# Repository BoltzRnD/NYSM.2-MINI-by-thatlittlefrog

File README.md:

# NYSM.2-MINI

NYSM.2 compatible full featured TMC2209 stepper driver with a smaller footprint than standard NYSM.2

It's around half the size of the original NYSM.2 driver, occupying a "2215" footprint rather than 2230, the smallest size seen on commercial M.2 drives.

### Future versions: 
* Cleaner routing
* Better thermals
* Custom low profile heatsink
* Onboard setting jumpers for microstepping

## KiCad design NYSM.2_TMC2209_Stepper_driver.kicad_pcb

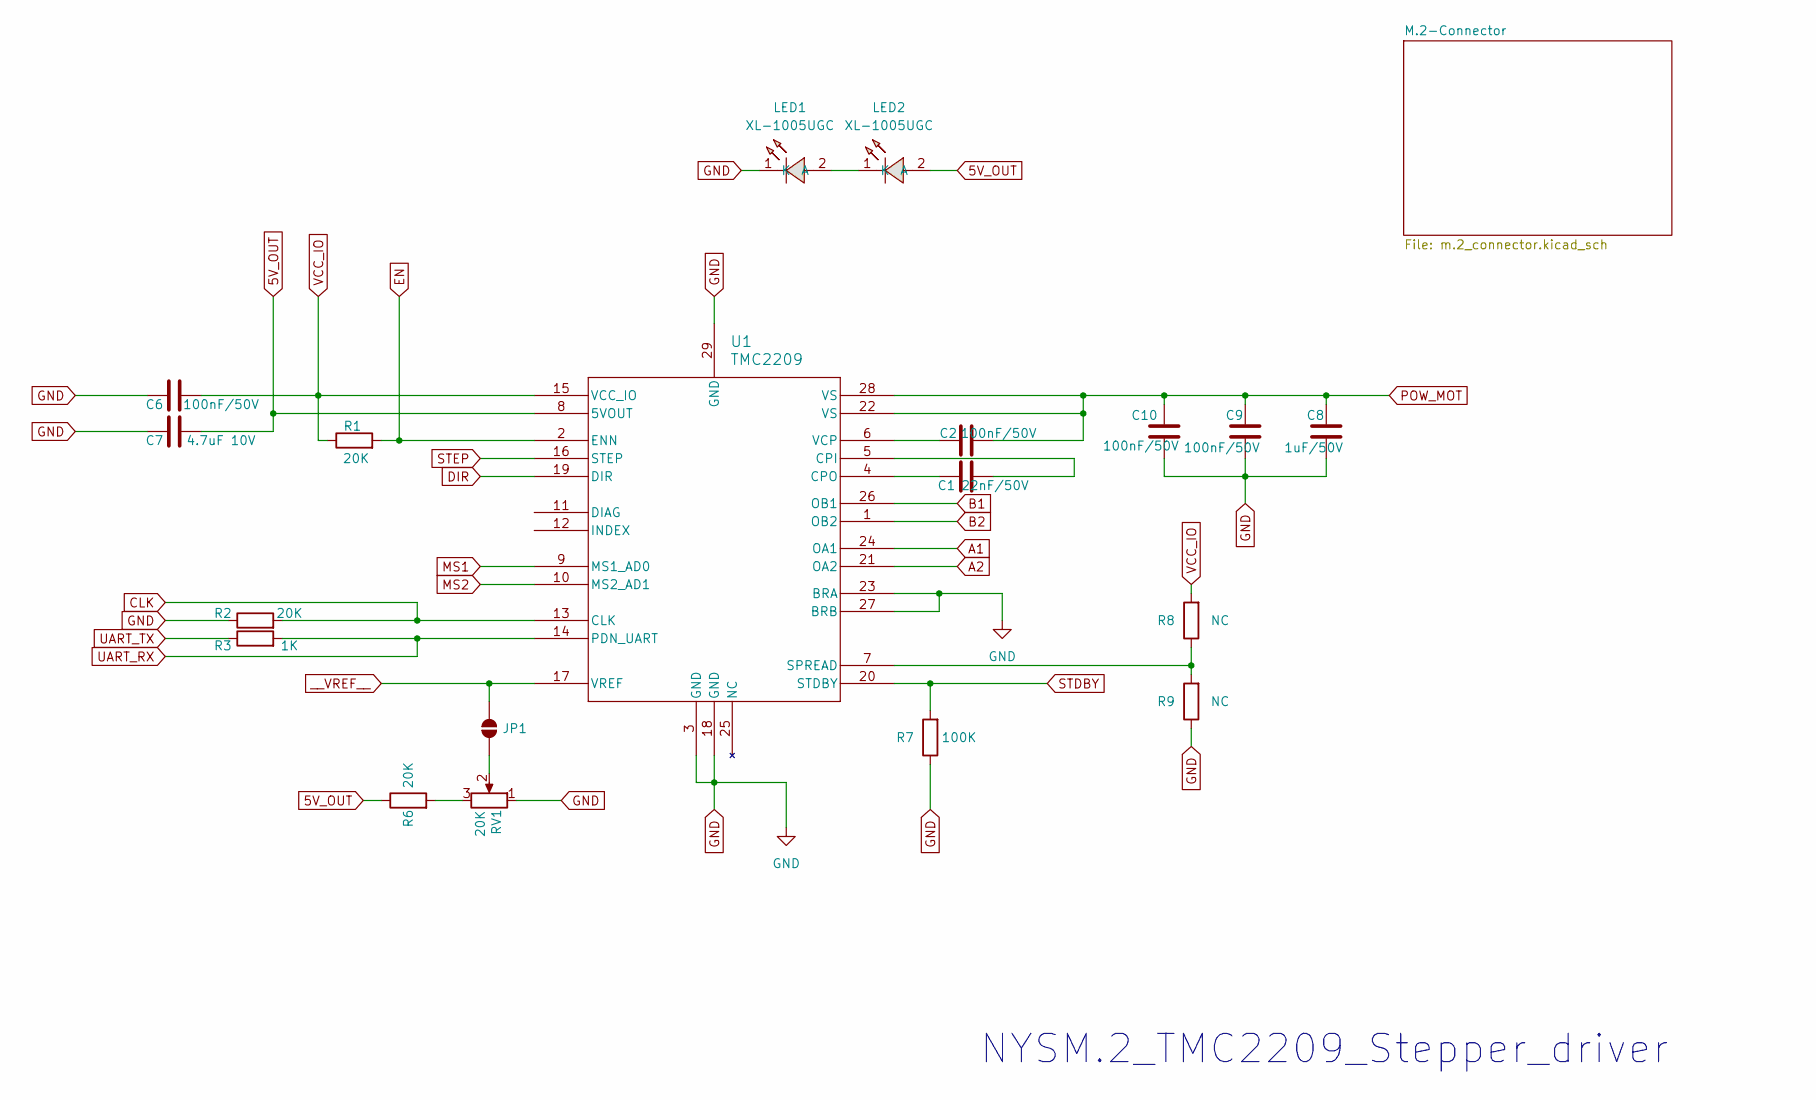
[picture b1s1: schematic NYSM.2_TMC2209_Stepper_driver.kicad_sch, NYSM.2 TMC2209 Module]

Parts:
C1: 22nF/50V; C_0402_1005Metric; Manufacturer_Part_Number CC0402KRX7R9BB223; LCSC# C107026
C2, C6, C9, C10: 100nF/50V; C_0402_1005Metric; Manufacturer_Part_Number 0402B104K500CT; LCSC# C152814
C7: 4.7uF 10V; C_0402_1005Metric; Manufacturer_Part_Number CL05A475KP5NRNC; LCSC# C368809
C8: 1uF/50V; C_0402_1005Metric; Manufacturer_Part_Number GRM155R61H105KE05D; LCSC# C1518208
JP1: SolderJumper-2_P1.3mm_Open_Pad1.0x1.5mm
LED1, LED2: XL-1005UGC; LED0402-RD_GREEN; LCSC Part C965793
R1, R2, R6: 20K; R_0402_1005Metric; Manufacturer_Part_Number WR04X203JTL; LCSC# C384364
R3: 1K; R_0402_1005Metric; Manufacturer_Part_Number WR04X1001FTL; LCSC# C163815
R7: 100K; R_0402_1005Metric; Manufacturer_Part_Number WR04X104JTL; LCSC# C384388
R8, R9: NC; R_0402_1005Metric
RV1: 20K; Potentiometer_Bourns_TC33X_Vertical; Manufacturer_Part_Number VG039NCHXTB203; LCSC# C128550
U1: TMC2209; QFN28_5X5_TRI; Manufacturer_Part_Number TMC2209; LCSC# C465949

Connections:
5V_OUT: C7.2, LED2.2 (A), R6.1, U1.8 (5VOUT)
A1: U1.24 (OA1); also elsewhere on the board
A2: U1.21 (OA2); also elsewhere on the board
B1: U1.26 (OB1); also elsewhere on the board
B2: U1.1 (OB2); also elsewhere on the board
CLK: R2.2, U1.13 (CLK); also elsewhere on the board
DIR: U1.19 (DIR); also elsewhere on the board
EN: R1.2, U1.2 (ENN); also elsewhere on the board
GND: C6.1, C7.1, C8.2, C9.2, C10.2, LED1.1 (K), R2.1, R7.1, R9.1, RV1.1, U1.3 (GND), U1.18 (GND), U1.23 (BRA), U1.27 (BRB), U1.29 (GND); also elsewhere on the board
MS1: U1.9 (MS1_AD0); also elsewhere on the board
MS2: U1.10 (MS2_AD1); also elsewhere on the board
unnamed: JP1.1 (A), RV1.2
unnamed: LED1.2 (A), LED2.1 (K)
unnamed: R6.2, RV1.3
unnamed: C1.2, U1.5 (CPI)
unnamed: C1.1, U1.4 (CPO)
unnamed: R8.1, R9.2, U1.7 (SPREAD)
unnamed: C2.1, U1.6 (VCP)
POW_MOT: C2.2, C8.1, C9.1, C10.1, U1.22 (VS), U1.28 (VS); also elsewhere on the board
STDBY: R7.2, U1.20 (STDBY); also elsewhere on the board
STEP: U1.16 (STEP); also elsewhere on the board
UART_RX: R3.2, U1.14 (PDN_UART); also elsewhere on the board
UART_TX: R3.1; also elsewhere on the board
VCC_IO: C6.2, R1.1, R8.2, U1.15 (VCC_IO); also elsewhere on the board
__VREF__: JP1.2 (B), U1.17 (VREF); also elsewhere on the board

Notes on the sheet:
NYSM.2_TMC2209_Stepper_driver

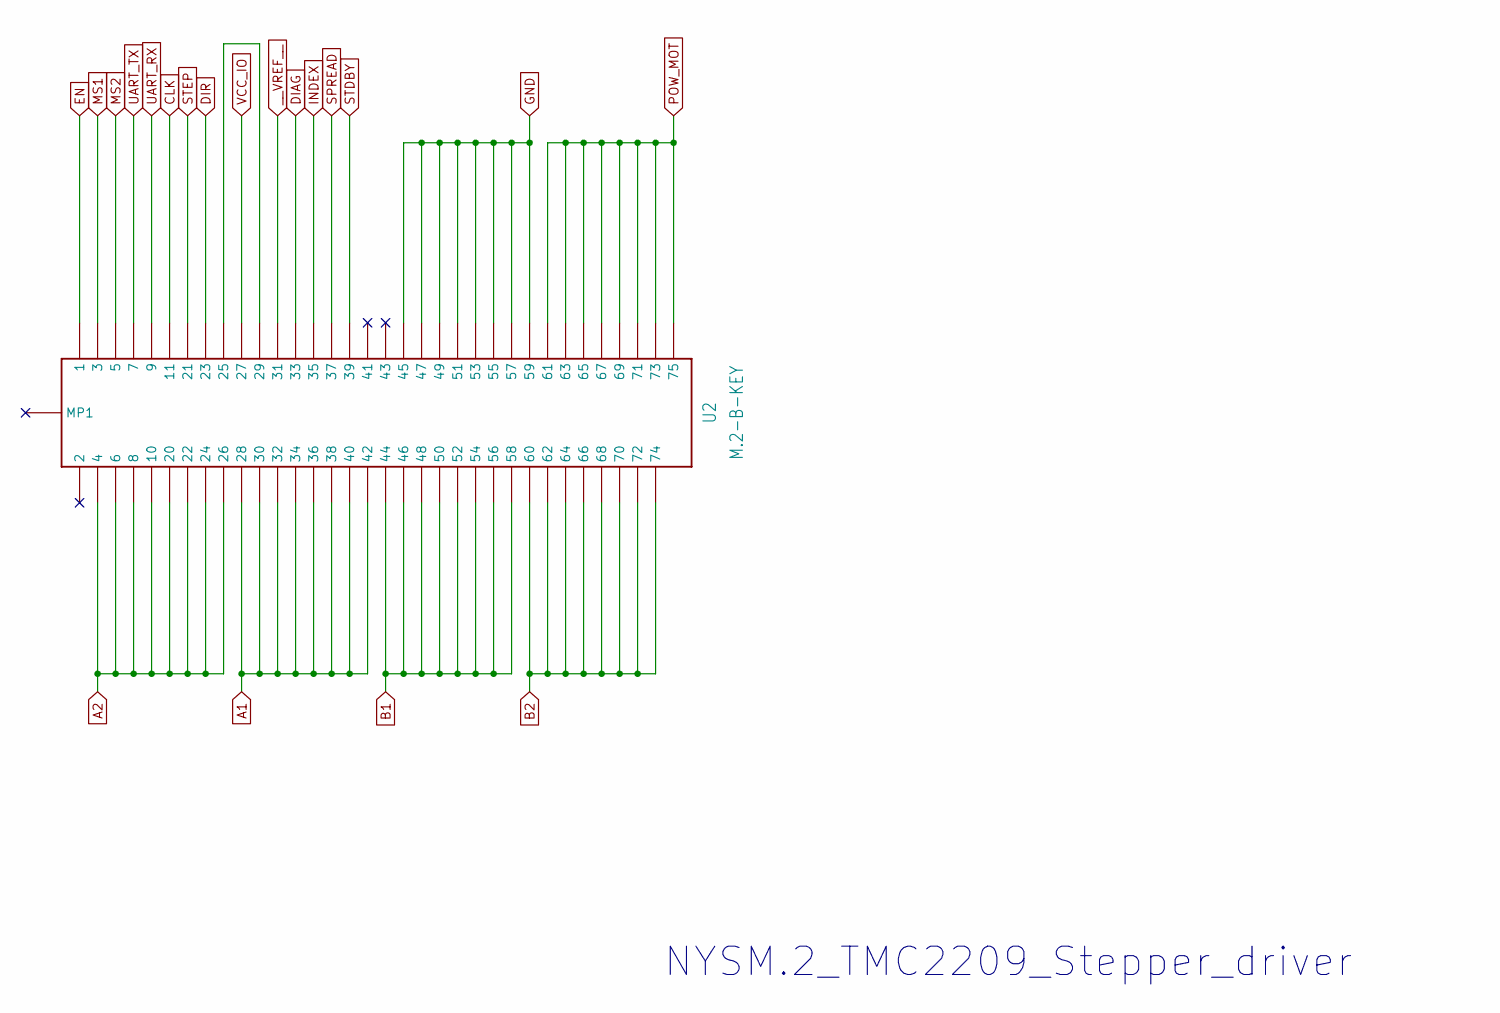
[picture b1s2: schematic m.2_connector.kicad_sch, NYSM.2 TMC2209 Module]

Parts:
U2: M.2-B-KEY; NYSM2-Card-B-Key

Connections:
A1: U2.P$28 (28), U2.P$30 (30), U2.P$32 (32), U2.P$34 (34), U2.P$36 (36), U2.P$38 (38), U2.P$40 (40), U2.P$42 (42); also elsewhere on the board
A2: U2.P$4 (4), U2.P$6 (6), U2.P$8 (8), U2.P$10 (10), U2.P$20 (20), U2.P$22 (22), U2.P$24 (24), U2.P$26 (26); also elsewhere on the board
B1: U2.P$44 (44), U2.P$46 (46), U2.P$48 (48), U2.P$50 (50), U2.P$52 (52), U2.P$54 (54), U2.P$56 (56), U2.P$58 (58); also elsewhere on the board
B2: U2.P$60 (60), U2.P$62 (62), U2.P$64 (64), U2.P$66 (66), U2.P$68 (68), U2.P$70 (70), U2.P$72 (72), U2.P$74 (74); also elsewhere on the board
CLK: U2.P$11 (11); also elsewhere on the board
DIAG: U2.P$33 (33)
DIR: U2.P$23 (23); also elsewhere on the board
EN: U2.P$1 (1); also elsewhere on the board
GND: U2.P$45 (45), U2.P$47 (47), U2.P$49 (49), U2.P$51 (51), U2.P$53 (53), U2.P$55 (55), U2.P$57 (57), U2.P$59 (59); also elsewhere on the board
INDEX: U2.P$35 (35)
MS1: U2.P$3 (3); also elsewhere on the board
MS2: U2.P$5 (5); also elsewhere on the board
unnamed: U2.P$25 (25), U2.P$29 (29)
POW_MOT: U2.P$61 (61), U2.P$63 (63), U2.P$65 (65), U2.P$67 (67), U2.P$69 (69), U2.P$71 (71), U2.P$73 (73), U2.P$75 (75); also elsewhere on the board
SPREAD: U2.P$37 (37)
STDBY: U2.P$39 (39); also elsewhere on the board
STEP: U2.P$21 (21); also elsewhere on the board
UART_RX: U2.P$9 (9); also elsewhere on the board
UART_TX: U2.P$7 (7); also elsewhere on the board
VCC_IO: U2.P$27 (27); also elsewhere on the board
__VREF__: U2.P$31 (31); also elsewhere on the board

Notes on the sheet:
NYSM.2_TMC2209_Stepper_driver

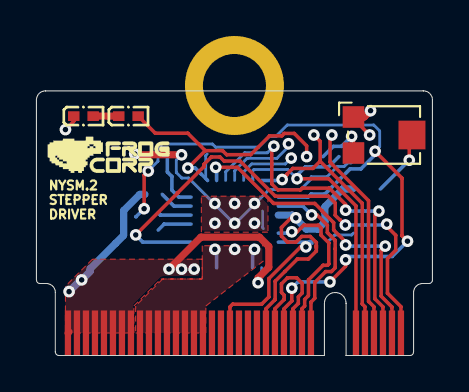
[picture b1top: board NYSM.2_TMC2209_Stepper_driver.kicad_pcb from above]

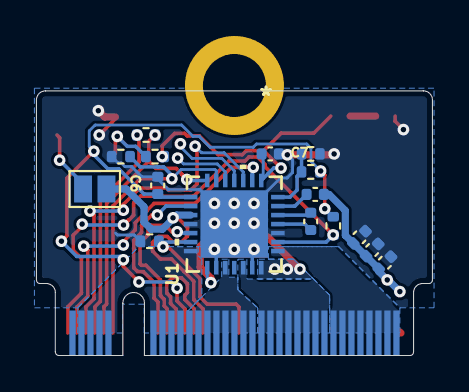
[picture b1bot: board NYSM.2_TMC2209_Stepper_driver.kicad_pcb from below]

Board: 2 copper layers, 22.0 x 14.7 mm, 20 parts (16 on the bottom side), 26 nets.

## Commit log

2025-04-23 Update LICENSE
2025-04-23 Uploaded files
2025-04-26 Update README.md
    improved readme

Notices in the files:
NYSM.2_TMC2209_Stepper_driver.kicad_sch:
License: This work is licensed under GPLV3
